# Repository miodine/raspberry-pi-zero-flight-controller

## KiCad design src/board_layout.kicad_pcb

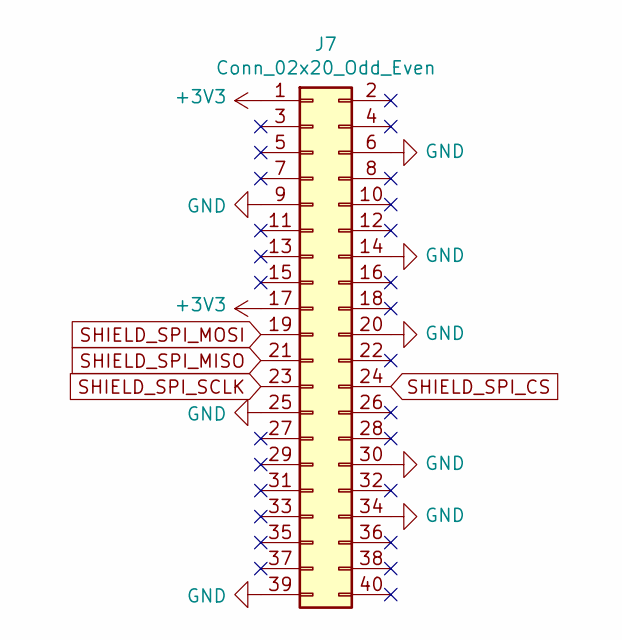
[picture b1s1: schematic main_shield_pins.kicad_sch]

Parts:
J7: Conn_02x20_Odd_Even; PinHeader_2x20_P2.54mm_Vertical

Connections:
GND: J7.6, J7.9, J7.14, J7.20, J7.25, J7.30, J7.34, J7.39; also elsewhere on the board
SHIELD_SPI_CS: J7.24; also elsewhere on the board
SHIELD_SPI_MISO: J7.21; also elsewhere on the board
SHIELD_SPI_MOSI: J7.19; also elsewhere on the board
SHIELD_SPI_SCLK: J7.23; also elsewhere on the board

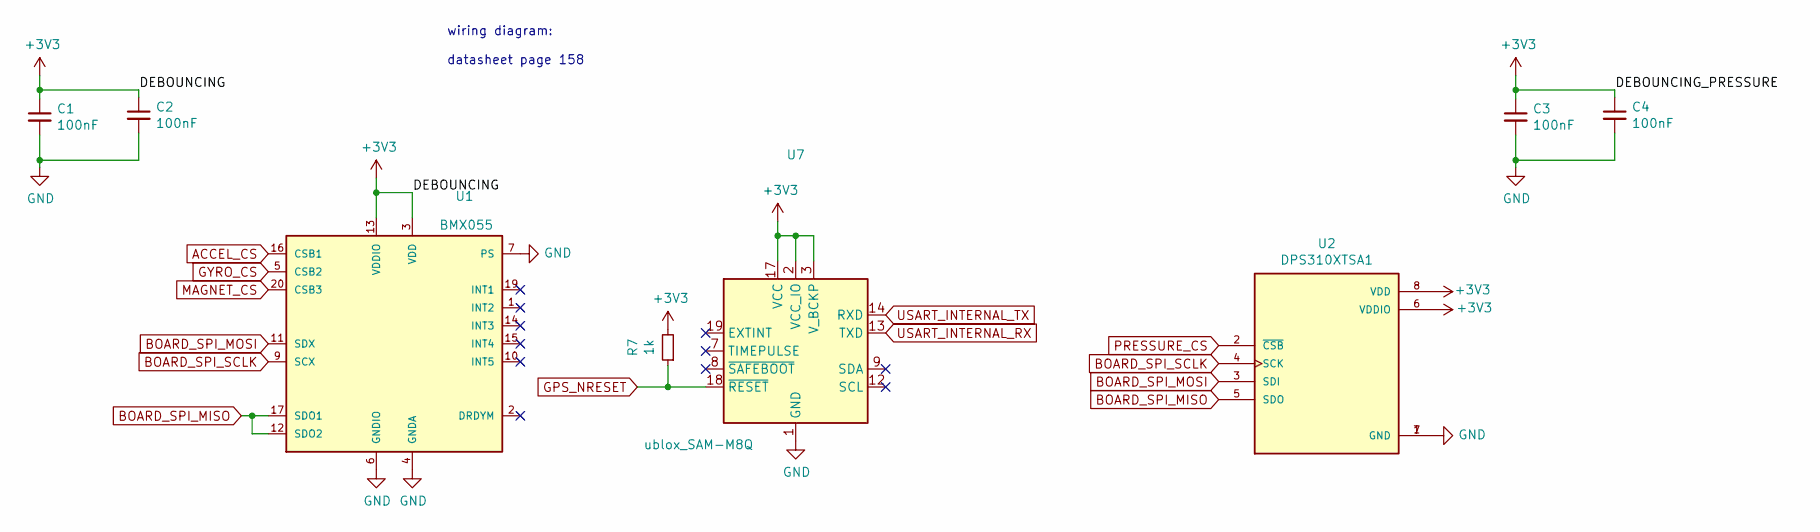
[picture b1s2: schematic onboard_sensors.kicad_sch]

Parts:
C1, C2, C3, C4: 100nF; C_0603_1608Metric
R7: 1k; R_0603_1608Metric
U1: BMX055
U2: DPS310XTSA1; XDCR_DPS310XTSA1
U7: ublox_SAM-M8Q

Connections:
ACCEL_CS: U1.16 (CSB1); also elsewhere on the board
BOARD_SPI_MISO: U1.12 (SDO2), U1.17 (SDO1), U2.5 (SDO); also elsewhere on the board
BOARD_SPI_MOSI: U1.11 (SDX), U2.3 (SDI); also elsewhere on the board
BOARD_SPI_SCLK: U1.9 (SCX), U2.4 (SCK); also elsewhere on the board
GND: C1.2, C2.2, C3.2, C4.2, U1.4 (GNDA), U1.6 (GNDIO), U1.7 (PS), U2.1 (GND), U2.7 (GND), U7.1 (GND), U7.4 (GND), U7.5 (GND), U7.6 (GND), U7.10 (GND), U7.11 (GND), U7.15 (GND), U7.16 (GND), U7.20 (GND); also elsewhere on the board
GPS_NRESET: R7.1, U7.18 (~RESET); also elsewhere on the board
GYRO_CS: U1.5 (CSB2); also elsewhere on the board
MAGNET_CS: U1.20 (CSB3); also elsewhere on the board
PRESSURE_CS: U2.2 (~CSB); also elsewhere on the board
USART_INTERNAL_RX: U7.13 (TXD); also elsewhere on the board
USART_INTERNAL_TX: U7.14 (RXD); also elsewhere on the board

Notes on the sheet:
wiring diagram: datasheet page 158

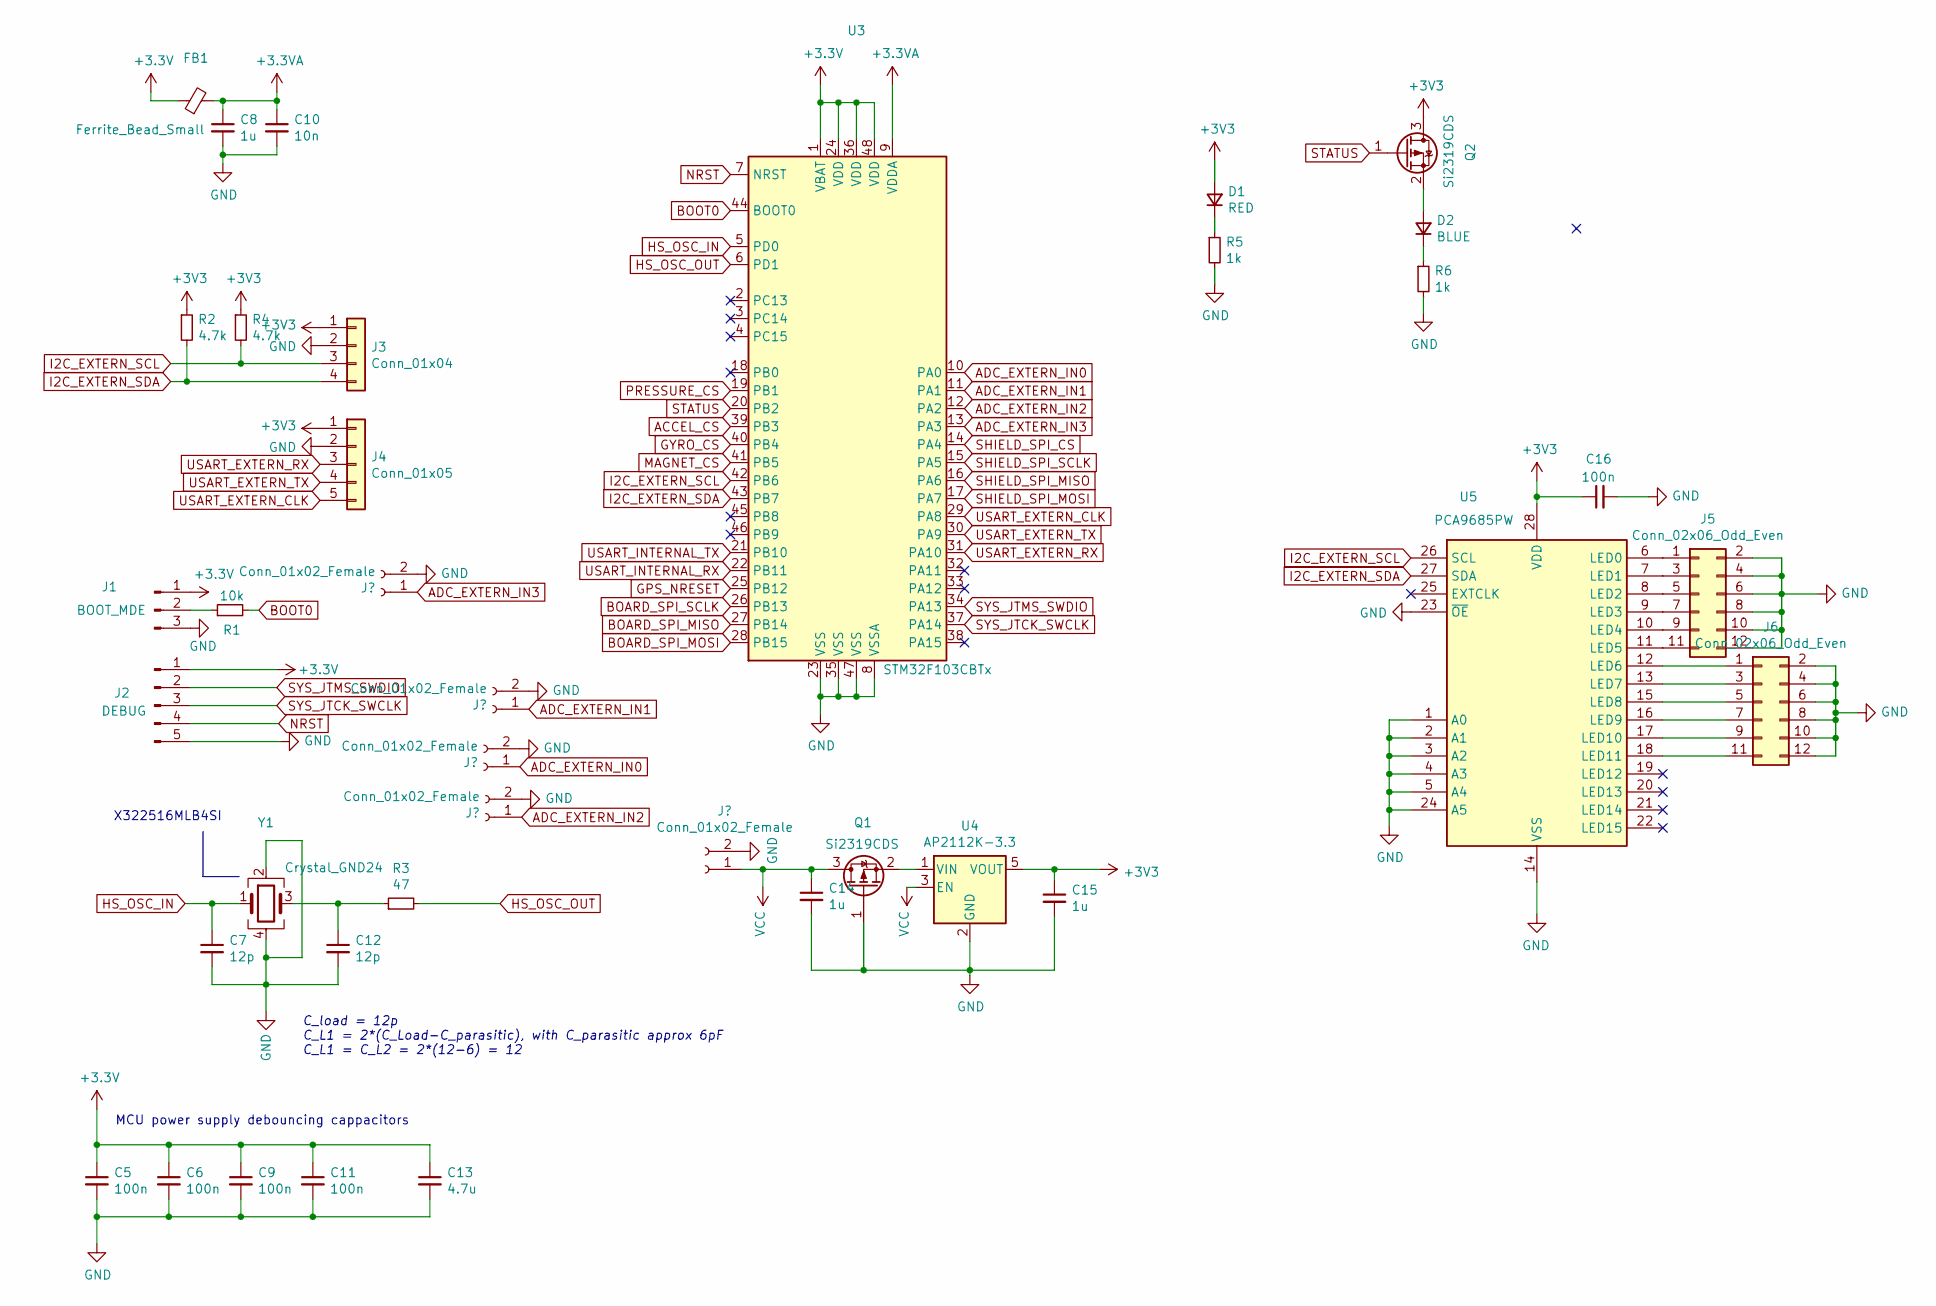
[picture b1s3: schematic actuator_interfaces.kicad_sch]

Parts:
C5, C6, C9, C11, C16: 100n; C_0603_1608Metric
C7, C12: 12p; C_0603_1608Metric
C8, C14, C15: 1u; C_0603_1608Metric
C10: 10n; C_0603_1608Metric
C13: 4.7u; C_0603_1608Metric
D1: RED; LED_0603_1608Metric_Pad1.05x0.95mm_HandSolder
D2: BLUE; LED_0603_1608Metric_Pad1.05x0.95mm_HandSolder
FB1: Ferrite_Bead_Small; R_0805_2012Metric
J1: BOOT_MDE; PinHeader_1x03_P2.54mm_Vertical
J2: DEBUG; PinHeader_1x05_P1.27mm_Vertical
J3: Conn_01x04; Molex_PicoBlade_53398-0471_1x04-1MP_P1.25mm_Vertical
J4: Conn_01x05; Molex_PicoBlade_53398-0571_1x05-1MP_P1.25mm_Vertical
J5, J6: Conn_02x06_Odd_Even; PinHeader_2x06_P2.54mm_Vertical
J8, J9, J10, J11, J12: Conn_01x02_Female; PinHeader_1x02_P2.54mm_Vertical
Q1, Q2: Si2319CDS; SOT-23
R1: 10k; R_0603_1608Metric
R2, R4: 4.7k; R_0603_1608Metric
R3: 47; R_0603_1608Metric
R5, R6: 1k; R_0603_1608Metric
U3: STM32F103CBTx; LQFP-48_7x7mm_P0.5mm
U4: AP2112K-3.3; SOT-23-5
U5: PCA9685PW; TSSOP-28_4.4x9.7mm_P0.65mm
Y1: Crystal_GND24; Crystal_SMD_3225-4Pin_3.2x2.5mm

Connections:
+3.3VA: C8.1, C10.1, FB1.2, U3.9 (VDDA)
ACCEL_CS: U3.39 (PB3); also elsewhere on the board
ADC_EXTERN_IN0: J9.1, U3.10 (PA0)
ADC_EXTERN_IN1: J11.1, U3.11 (PA1)
ADC_EXTERN_IN2: J10.1, U3.12 (PA2)
ADC_EXTERN_IN3: J8.1, U3.13 (PA3)
BOARD_SPI_MISO: U3.27 (PB14); also elsewhere on the board
BOARD_SPI_MOSI: U3.28 (PB15); also elsewhere on the board
BOARD_SPI_SCLK: U3.26 (PB13); also elsewhere on the board
BOOT0: R1.2, U3.44 (BOOT0)
GND: C5.2, C6.2, C7.2, C8.2, C9.2, C10.2, C11.2, C12.2, C13.2, C14.2, C15.2, C16.2, J1.3, J2.5, J3.2, J4.2, J5.2, J5.4, J5.6, J5.8, J5.10, J5.12, J6.2, J6.4, J6.6, J6.8, J6.10, J6.12, J8.2, J9.2, J10.2, J11.2, J12.2, Q1.1 (G), R5.2, R6.2, U3.8 (VSSA), U3.23 (VSS), U3.35 (VSS), U3.47 (VSS), U4.2 (GND), U5.1 (A0), U5.2 (A1), U5.3 (A2), U5.4 (A3), U5.5 (A4), U5.14 (VSS), U5.23 (~OE), U5.24 (A5), Y1.2, Y1.4; also elsewhere on the board
GPS_NRESET: U3.25 (PB12); also elsewhere on the board
GYRO_CS: U3.40 (PB4); also elsewhere on the board
HS_OSC_IN: C7.1, U3.5 (PD0), Y1.1
HS_OSC_OUT: R3.2, U3.6 (PD1)
I2C_EXTERN_SCL: J3.3, R4.2, U3.42 (PB6), U5.26 (SCL)
I2C_EXTERN_SDA: J3.4, R2.2, U3.43 (PB7), U5.27 (SDA)
MAGNET_CS: U3.41 (PB5); also elsewhere on the board
NRST: J2.4, U3.7 (NRST)
unnamed: C12.1, R3.1, Y1.3
unnamed: D1.1 (K), R5.1
unnamed: D2.1 (K), R6.1
unnamed: D2.2 (A), Q2.2 (S)
unnamed: J1.2, R1.1
unnamed: J5.1, U5.6 (LED0)
unnamed: J5.3, U5.7 (LED1)
unnamed: J5.5, U5.8 (LED2)
unnamed: J5.7, U5.9 (LED3)
unnamed: J5.9, U5.10 (LED4)
unnamed: J5.11, U5.11 (LED5)
unnamed: J6.1, U5.12 (LED6)
unnamed: J6.3, U5.13 (LED7)
unnamed: J6.5, U5.15 (LED8)
unnamed: J6.7, U5.16 (LED9)
unnamed: J6.9, U5.17 (LED10)
unnamed: J6.11, U5.18 (LED11)
unnamed: Q1.2 (S), U4.1 (VIN)
PRESSURE_CS: U3.19 (PB1); also elsewhere on the board
SHIELD_SPI_CS: U3.14 (PA4); also elsewhere on the board
SHIELD_SPI_MISO: U3.16 (PA6); also elsewhere on the board
SHIELD_SPI_MOSI: U3.17 (PA7); also elsewhere on the board
SHIELD_SPI_SCLK: U3.15 (PA5); also elsewhere on the board
STATUS: Q2.1 (G), U3.20 (PB2)
SYS_JTCK_SWCLK: J2.3, U3.37 (PA14)
SYS_JTMS_SWDIO: J2.2, U3.34 (PA13)
USART_EXTERN_CLK: J4.5, U3.29 (PA8)
USART_EXTERN_RX: J4.3, U3.31 (PA10)
USART_EXTERN_TX: J4.4, U3.30 (PA9)
USART_INTERNAL_RX: U3.22 (PB11); also elsewhere on the board
USART_INTERNAL_TX: U3.21 (PB10); also elsewhere on the board
VCC: C14.1, J12.1, Q1.3 (D), U4.3 (EN)

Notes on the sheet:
C_load = 12p C_L1 = 2*(C_Load-C_parasitic), with C_parasitic approx 6pF C_L1 = C_L2 = 2*(12-6) = 12
X322516MLB4SI
MCU power supply debouncing cappacitors

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
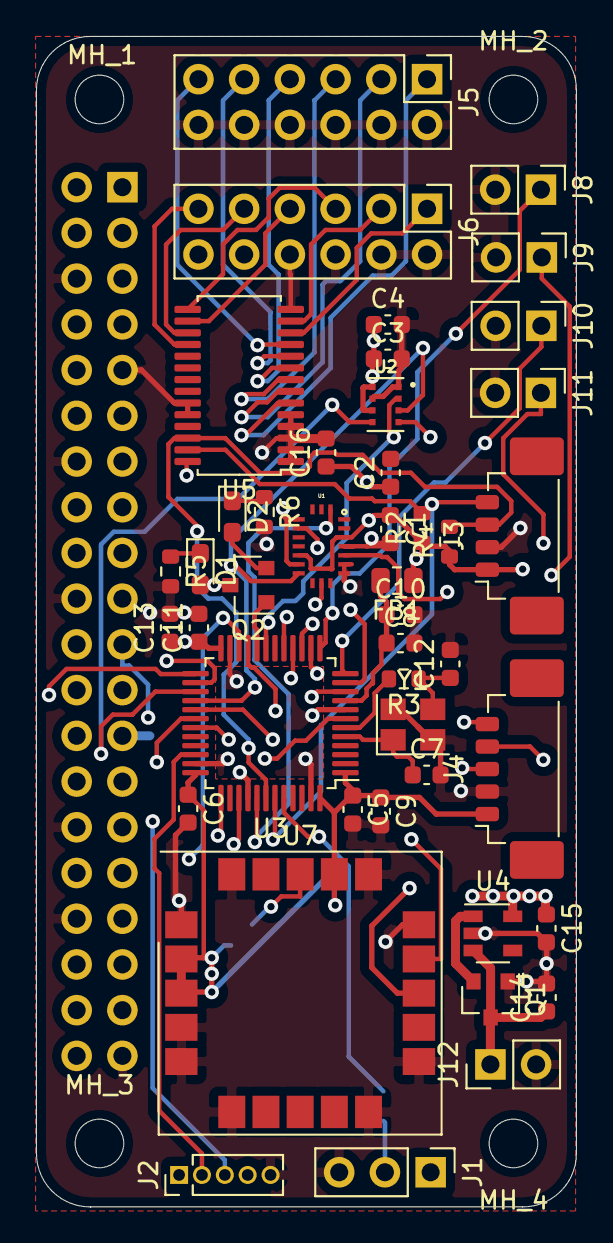
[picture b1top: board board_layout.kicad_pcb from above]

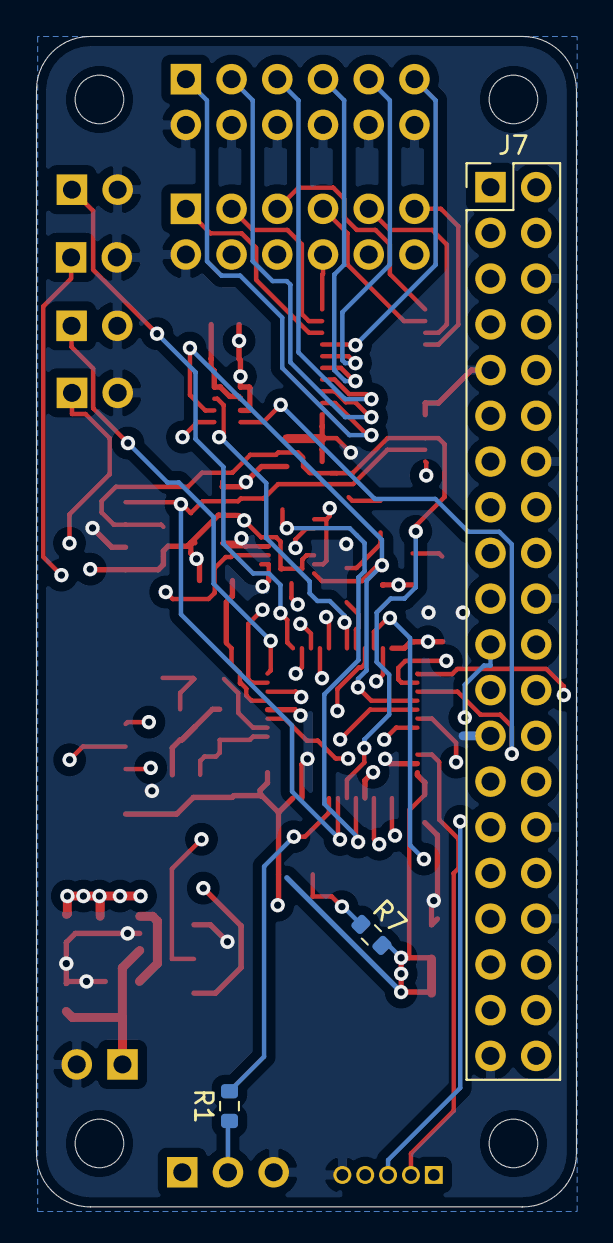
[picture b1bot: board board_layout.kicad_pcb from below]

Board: 4 copper layers, 30.0 x 65.0 mm, 51 parts (3 on the bottom side), 52 nets.

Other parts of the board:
MH_1, MH_2, MH_3, MH_4: MountingHole_2.7mm_M2.5_ISO7380

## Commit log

2024-12-29 [DEV] Initial Design
    Add circuit diagram, base PCB layout and project outline
2024-12-29 [DEVMINOR] Reorganization of the circuit diagram
    Adding dividers and labels to subsections of the project
2024-12-30 [DEVMINOR] Ignore backups
